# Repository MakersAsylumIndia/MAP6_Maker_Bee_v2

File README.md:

# MAP6_Maker_Bee_v2
Learn to solder course ware. Blinky LEDs and vibration motor driven by a 555. Shaped like a Honey Bee

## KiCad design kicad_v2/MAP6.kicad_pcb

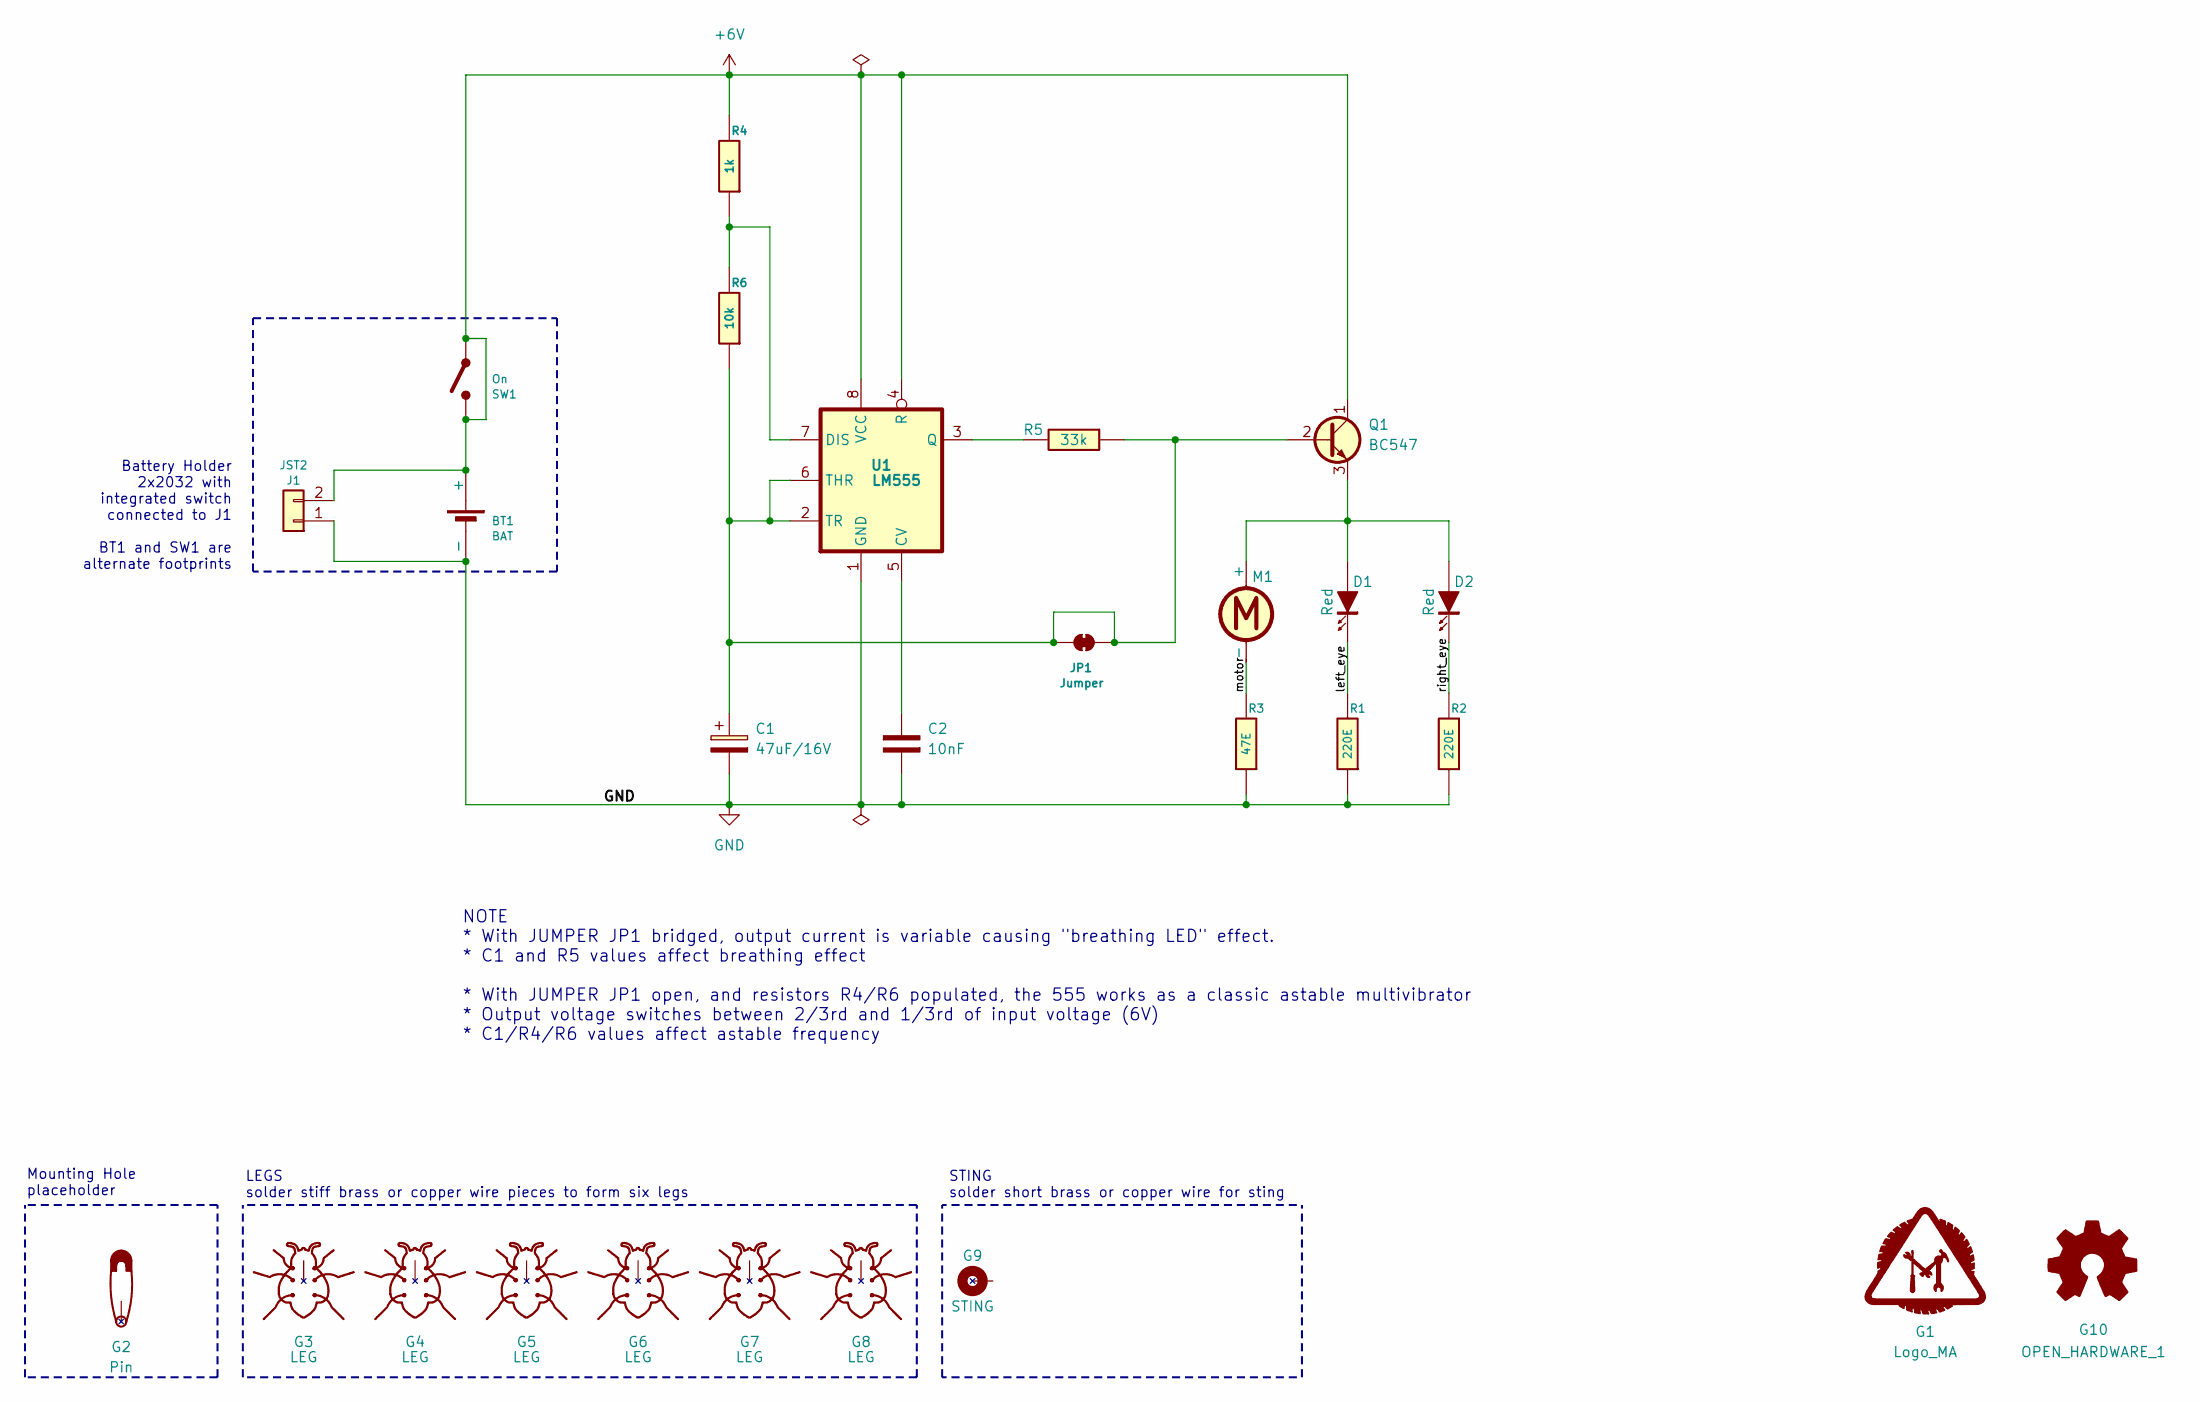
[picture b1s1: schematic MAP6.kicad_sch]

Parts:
BT1: BAT; cr2032_03
C1: 47uF/16V; CP_Radial_D6.3mm_P2.50mm
C2: 10nF; C_Disc_D5.0mm_W2.5mm_P2.50mm
D1: Red; LED-5MM_left
D2: Red; LED-5MM_right
G1: Logo_MA; MA_LOGO
G2: Pin; MTG_2mm
G3, G4, G5, G6, G7, G8: LEG; MTG_1mm_5mm_LEG
G9: STING; MTG_1mm
G10: OPEN_HARDWARE_1; Logo_silk_OSHW_6x6mm
J1: JST2; JST_EH_B2B-EH-A_1x02_P2.50mm_Vertical
JP1: Jumper; SolderJumper-2_P1.3mm_Open_RoundedPad1.0x1.5mm
M1: Motor; motor_XDCR_C0720B001F
Q1: BC547; TO-92L_Wide
R1, R2: 220E; Resistor_Horizontal_0.3in
R3: 47E; Resistor_Horizontal_0.3in
R4: 1k; Resistor_Horizontal_0.3in
R5: 33k; Resistor_Horizontal_0.3in
R6: 10k; Resistor_Horizontal_0.3in
SW1: On; SW_SPDT_Straight
U1: LM555; DIP-8_W7.62mm

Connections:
+6V: BT1.1 (+), J1.2, Q1.1 (C), R4.2, SW1.1 (A), SW1.2 (B), U1.4 (R), U1.8 (VCC)
/left_eye: D1.2 (K), R1.2
/motor: M1.2 (-), R3.2
/right_eye: D2.2 (K), R2.2
GND: BT1.2 (-), C1.2, C2.2, J1.1, R1.1, R2.1, R3.1, U1.1 (GND)
unnamed: D1.1 (A), D2.1 (A), M1.1 (+), Q1.3 (E)
unnamed: C1.1, JP1.1 (A), JP1.2 (B), Q1.2 (B), R5.1, R6.1, U1.2 (TR), U1.6 (THR)
unnamed: C2.1, U1.5 (CV)
unnamed: R4.1, R6.2, U1.7 (DIS)
unnamed: R5.2, U1.3 (Q)

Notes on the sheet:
NOTE * With JUMPER JP1 bridged, output current is variable causing "breathing LED" effect. * C1 and R5 values affect breathing effect * With JUMPER JP1 open, and resistors R4/R6 populated, the 555 works as a classic astable multivibrator * Output voltage switches between 2/3rd and 1/3rd of input vo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
Mounting Hole placeholder
STING solder short brass or copper wire for sting
LEGS solder stiff brass or copper wire pieces to form six legs
Battery Holder 2x2032 with integrated switch connected to J1 BT1 and SW1 are alternate footprints

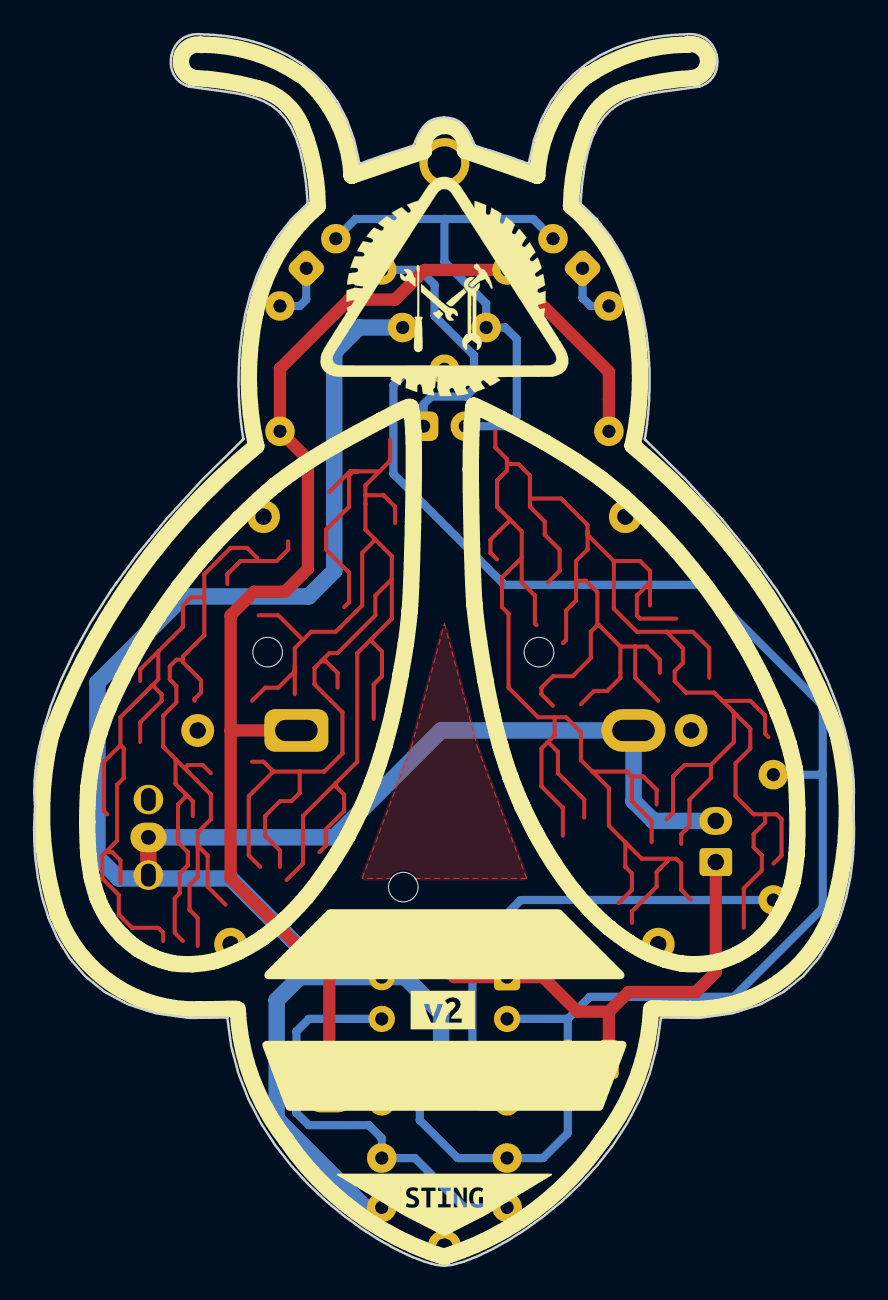
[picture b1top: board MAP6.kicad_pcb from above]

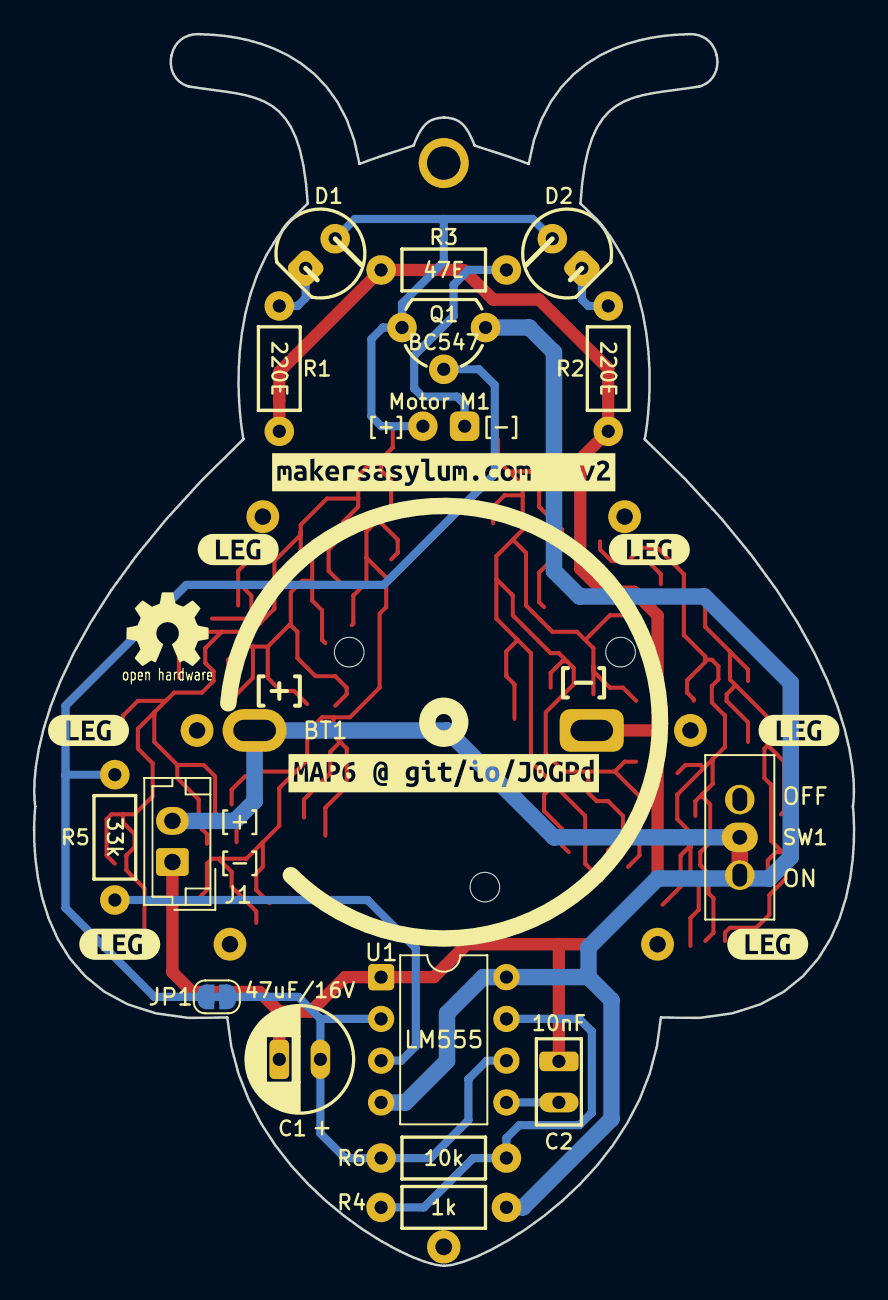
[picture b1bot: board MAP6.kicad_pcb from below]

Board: 2 copper layers, 49.9 x 74.9 mm, 37 parts (25 on the bottom side), 10 nets.

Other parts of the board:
kibuzzard-6A8BD39C: G***; kibuzzard-6A8BD39C
kibuzzard-6A8BF0DA: G***; kibuzzard-6A8BF0DA
kibuzzard-6A8BF0E4: G***; kibuzzard-6A8BF0E4
kibuzzard-6A8BF0EC: G***; kibuzzard-6A8BF0EC
kibuzzard-6A8BF0F1: G***; kibuzzard-6A8BF0F1
kibuzzard-6A8BF0F8: G***; kibuzzard-6A8BF0F8
kibuzzard-6A8BF0FF: G***; kibuzzard-6A8BF0FF
kibuzzard-6A8C194D: G***; kibuzzard-6A8C194D
kibuzzard-6A93D55D: G***; kibuzzard-6A93D55D
kibuzzard-6A903359: G***; kibuzzard-6A903359
